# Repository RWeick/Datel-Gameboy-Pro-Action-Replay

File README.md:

# Datel-Gameboy-Pro-Action-Replay
Everything necessary to produce the Pro Action Replay for the Gameboy.

PCB Thickness: 0.8 mm

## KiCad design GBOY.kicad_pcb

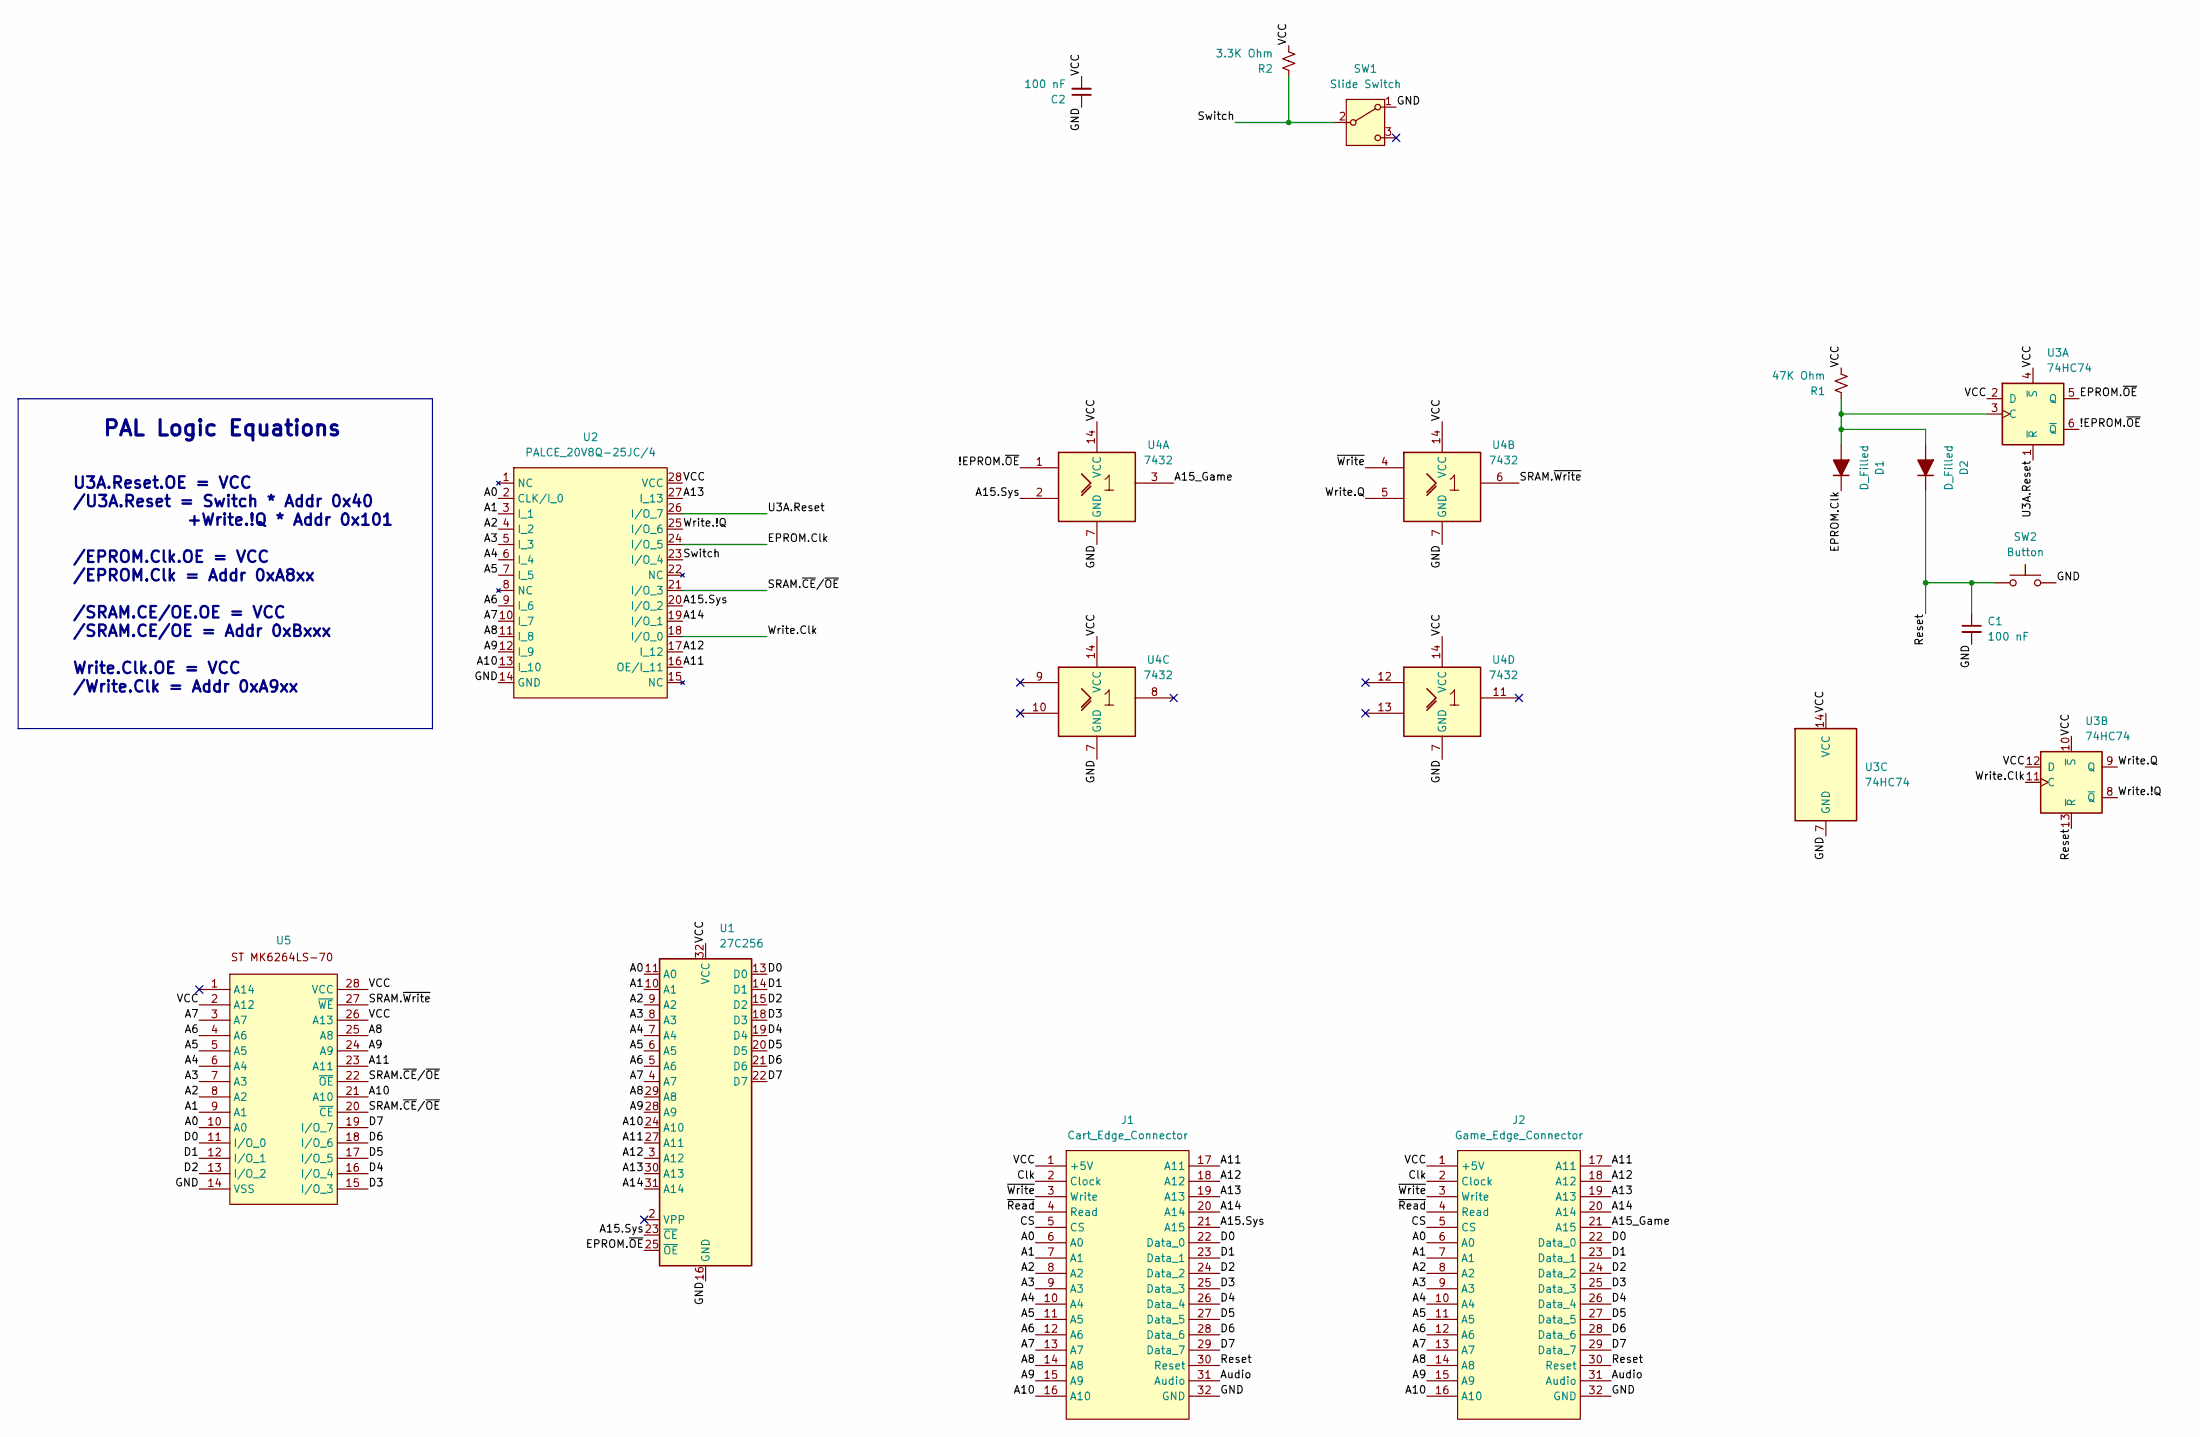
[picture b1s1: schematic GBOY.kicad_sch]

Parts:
C1, C2: 100 nF; 1206 SMD
D1, D2: D_Filled; 1206 SMD
J1: Cart_Edge_Connector; Edge Connector
J2: Game_Edge_Connector; Cartridge Slot
R1: 47K Ohm; 1206 SMD
R2: 3.3K Ohm; 1206 SMD
SW1: Slide Switch; Switch
SW2: Button
U1: 27C256; EPROM
U2: PALCE_20V8Q-25JC/4; PALCE
U3: 74HC74; SOIC-14
U4: 7432; SOIC-14
U5: SRAM

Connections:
/!EPROM.~OE: U3.6 (~Q), U4.1
/A0: J1.6 (A0), J2.6 (A0), U1.11 (A0), U2.2 (CLK/I_0), U5.10 (A0)
/A1: J1.7 (A1), J2.7 (A1), U1.10 (A1), U2.3 (I_1), U5.9 (A1)
/A2: J1.8 (A2), J2.8 (A2), U1.9 (A2), U2.4 (I_2), U5.8 (A2)
/A3: J1.9 (A3), J2.9 (A3), U1.8 (A3), U2.5 (I_3), U5.7 (A3)
/A4: J1.10 (A4), J2.10 (A4), U1.7 (A4), U2.6 (I_4), U5.6 (A4)
/A5: J1.11 (A5), J2.11 (A5), U1.6 (A5), U2.7 (I_5), U5.5 (A5)
/A6: J1.12 (A6), J2.12 (A6), U1.5 (A6), U2.9 (I_6), U5.4 (A6)
/A7: J1.13 (A7), J2.13 (A7), U1.4 (A7), U2.10 (I_7), U5.3 (A7)
/A8: J1.14 (A8), J2.14 (A8), U1.29 (A8), U2.11 (I_8), U5.25 (A8)
/A9: J1.15 (A9), J2.15 (A9), U1.28 (A9), U2.12 (I_9), U5.24 (A9)
/A10: J1.16 (A10), J2.16 (A10), U1.24 (A10), U2.13 (I_10), U5.21 (A10)
/A11: J1.17 (A11), J2.17 (A11), U1.27 (A11), U2.16 (OE/I_11), U5.23 (A11)
/A12: J1.18 (A12), J2.18 (A12), U1.3 (A12), U2.17 (I_12)
/A13: J1.19 (A13), J2.19 (A13), U1.30 (A13), U2.27 (I_13)
/A14: J1.20 (A14), J2.20 (A14), U1.31 (A14), U2.19 (I/O_1)
/A15.Sys: J1.21 (A15), U1.23 (~CE), U2.20 (I/O_2), U4.2
/A15_Game: J2.21 (A15), U4.3
/Audio: J1.31 (Audio), J2.31 (Audio)
/CS: J1.5 (CS), J2.5 (CS)
/Clk: J1.2 (Clock), J2.2 (Clock)
/D0: J1.22 (Data_0), J2.22 (Data_0), U1.13 (D0), U5.11 (I/O_0)
/D1: J1.23 (Data_1), J2.23 (Data_1), U1.14 (D1), U5.12 (I/O_1)
/D2: J1.24 (Data_2), J2.24 (Data_2), U1.15 (D2), U5.13 (I/O_2)
/D3: J1.25 (Data_3), J2.25 (Data_3), U1.18 (D3), U5.15 (I/O_3)
/D4: J1.26 (Data_4), J2.26 (Data_4), U1.19 (D4), U5.16 (I/O_4)
/D5: J1.27 (Data_5), J2.27 (Data_5), U1.20 (D5), U5.17 (I/O_5)
/D6: J1.28 (Data_6), J2.28 (Data_6), U1.21 (D6), U5.18 (I/O_6)
/D7: J1.29 (Data_7), J2.29 (Data_7), U1.22 (D7), U5.19 (I/O_7)
/EPROM.Clk: D1.1 (K), U2.24 (I/O_5)
/EPROM.~OE: U1.25 (~OE), U3.5 (Q)
/GND: C1.2, C2.1, J1.32 (GND), J2.32 (GND), SW1.1 (A), SW2.2, U1.16 (GND), U2.14 (GND), U3.7 (GND), U4.7 (GND), U5.14 (VSS)
/Reset: C1.1, D2.1 (K), J1.30 (Reset), J2.30 (Reset), SW2.1, U3.13 (~R)
/SRAM.~CE/~OE: U2.21 (I/O_3), U5.20 (~CE), U5.22 (~OE)
/SRAM.~Write: U4.6, U5.27 (~WE)
/Switch: R2.1, SW1.2 (B), U2.23 (I/O_4)
/U3A.Reset: U2.26 (I/O_7), U3.1 (~R)
/VCC: C2.2, J1.1 (+5V), J2.1 (+5V), R1.2, R2.2, U1.32 (VCC), U2.28 (VCC), U3.2 (D), U3.4 (~S), U3.10 (~S), U3.12 (D), U3.14 (VCC), U4.14 (VCC), U5.2 (A12), U5.26 (A13), U5.28 (VCC)
/Write.!Q: U2.25 (I/O_6), U3.8 (~Q)
/Write.Clk: U2.18 (I/O_0), U3.11 (C)
/Write.Q: U3.9 (Q), U4.5
/~Read: J1.4 (Read), J2.4 (Read)
/~Write: J1.3 (Write), J2.3 (Write), U4.4
unnamed: D1.2 (A), D2.2 (A), R1.1, U3.3 (C)

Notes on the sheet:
PAL Logic Equations
U3A.Reset.OE = VCC /U3A.Reset = Switch * Addr 0x40 +Write.!Q * Addr 0x101 /EPROM.Clk.OE = VCC /EPROM.Clk = Addr 0xA8xx /SRAM.CE/OE.OE = VCC /SRAM.CE/OE = Addr 0xBxxx Write.Clk.OE = VCC /Write.Clk = Addr 0xA9xx

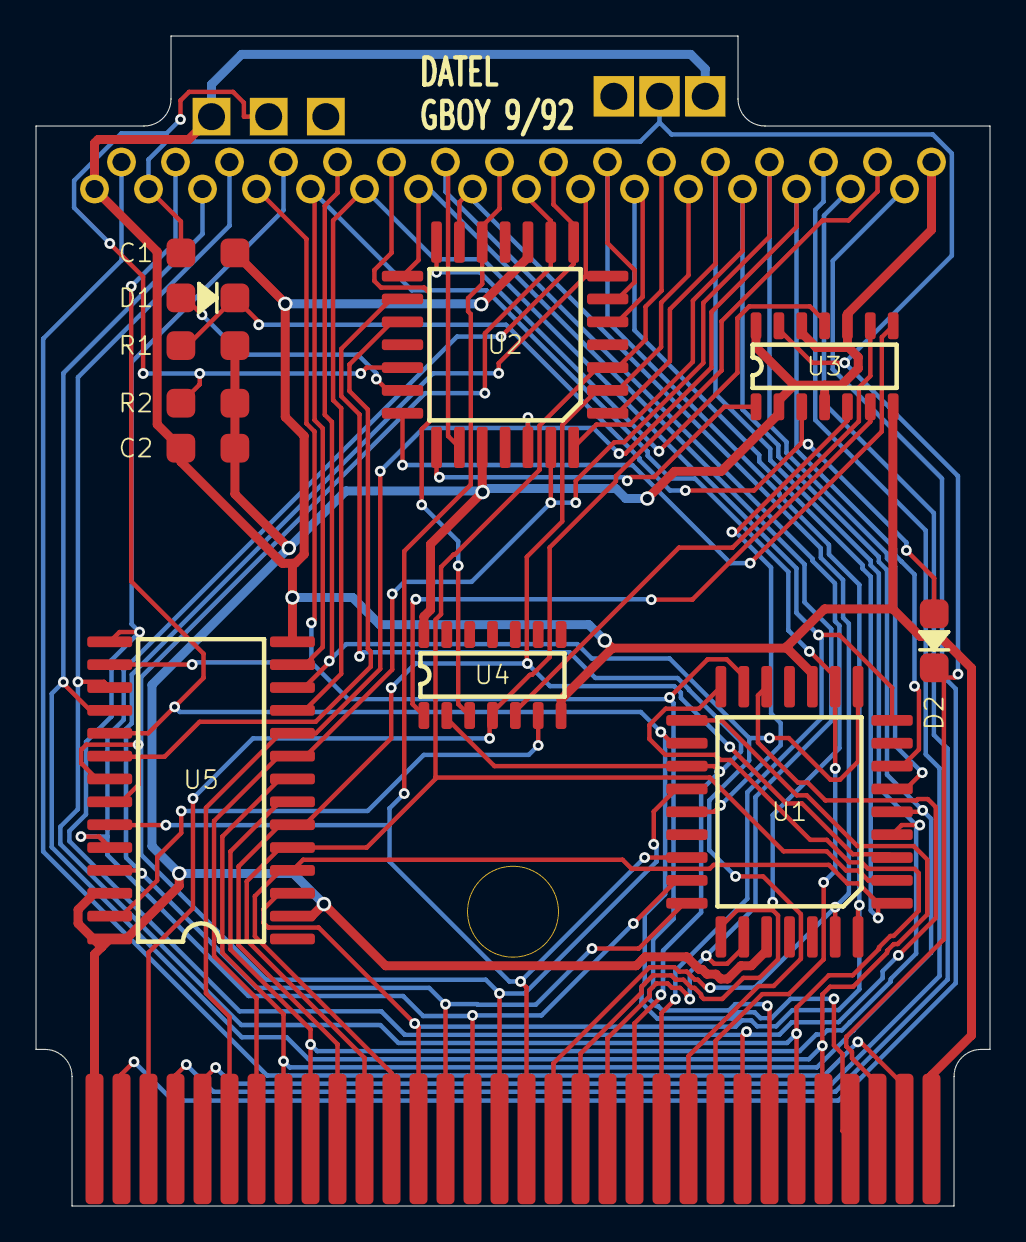
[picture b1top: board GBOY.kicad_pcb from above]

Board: 2 copper layers, 53.0 x 65.0 mm, 16 parts (0 on the bottom side), 44 nets.

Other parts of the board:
Hole: Drill Hole
